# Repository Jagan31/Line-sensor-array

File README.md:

# PCB design of line sensor array in eagle software
1)LSA2.sch is the schematic file of the line sensor array.

2)LSA2.brd is the pcb layout file of the line sensor array.

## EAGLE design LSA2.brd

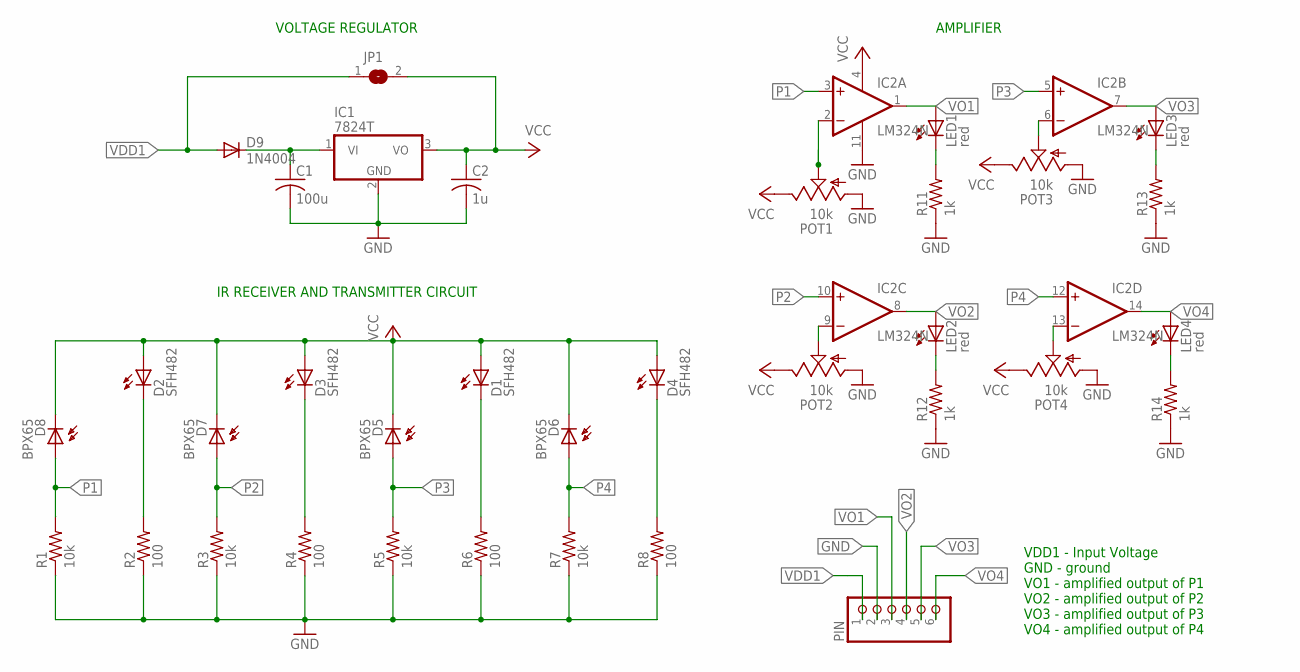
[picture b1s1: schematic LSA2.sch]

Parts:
C1: 100u; C0805
C2: 1u; C0805
D1, D2, D3, D4: SFH482
D5, D6, D7, D8: BPX65
D9: 1N4004; DO41-10
IC1: 7824T; TO220H
IC2: LM324N; DIL14
JP1: SJW
LED1, LED2, LED3, LED4: red; SMARTLED-TTW
PIN: PINHD-1X6/90; 1X06/90
POT1, POT2, POT3, POT4: 10k; 6MM
R1, R3, R5, R7: 10k; M0805
R2, R4, R6, R8: 100; M0805
R11, R12, R13, R14: 1k; M0805

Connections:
D5: D1.K (C), R6.2
GND: C1.2, C2.2, IC1.2 (GND), IC2.11 (V-), PIN.2, POT1.A, POT2.A, POT3.A, POT4.A, R11.1, R12.1, R13.1, R14.1
unnamed: C1.1, D9.C, IC1.1 (VI)
unnamed: D2.K (C), R2.2
unnamed: D3.K (C), R4.2
unnamed: D4.K (C), R8.2
unnamed: IC2.2 (-IN), POT1.S
unnamed: IC2.6 (-IN), POT3.S
unnamed: IC2.13 (-IN), POT4.S
unnamed: LED2.C@1 (C), R12.2
unnamed: LED4.C@1 (C), R14.2
unnamed: LED3.C@1 (C), R13.2
unnamed: LED1.C@1 (C), R11.2
P1: D8.A, IC2.3 (+IN), R1.2
P2: D7.A, IC2.10 (+IN), R3.2
P3: D5.A, IC2.5 (+IN), R5.2
P4: D6.A, IC2.12 (+IN), R7.2
POT2: IC2.9 (-IN), POT2.S
R6: R1.1, R2.1, R3.1, R4.1, R5.1, R6.1, R7.1, R8.1
VCC: C2.1, D1.A, D2.A, D3.A, D4.A, D5.K (C), D6.K (C), D7.K (C), D8.K (C), IC1.3 (VO), IC2.4 (V+), JP1.2, POT1.E, POT2.E, POT3.E, POT4.E
VDD1: D9.A, JP1.1, PIN.1
VO1: IC2.1 (OUT), LED1.A@1 (A), PIN.3
VO2: IC2.8 (OUT), LED2.A@1 (A), PIN.4
VO3: IC2.7 (OUT), LED3.A@1 (A), PIN.5
VO4: IC2.14 (OUT), LED4.A@1 (A), PIN.6

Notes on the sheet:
VOLTAGE REGULATOR
AMPLIFIER
VDD1 - Input Voltage GND - ground VO1 - amplified output of P1 VO2 - amplified output of P2 VO3 - amplified output of P3 VO4 - amplified output of P4
IR RECEIVER AND TRANSMITTER CIRCUIT

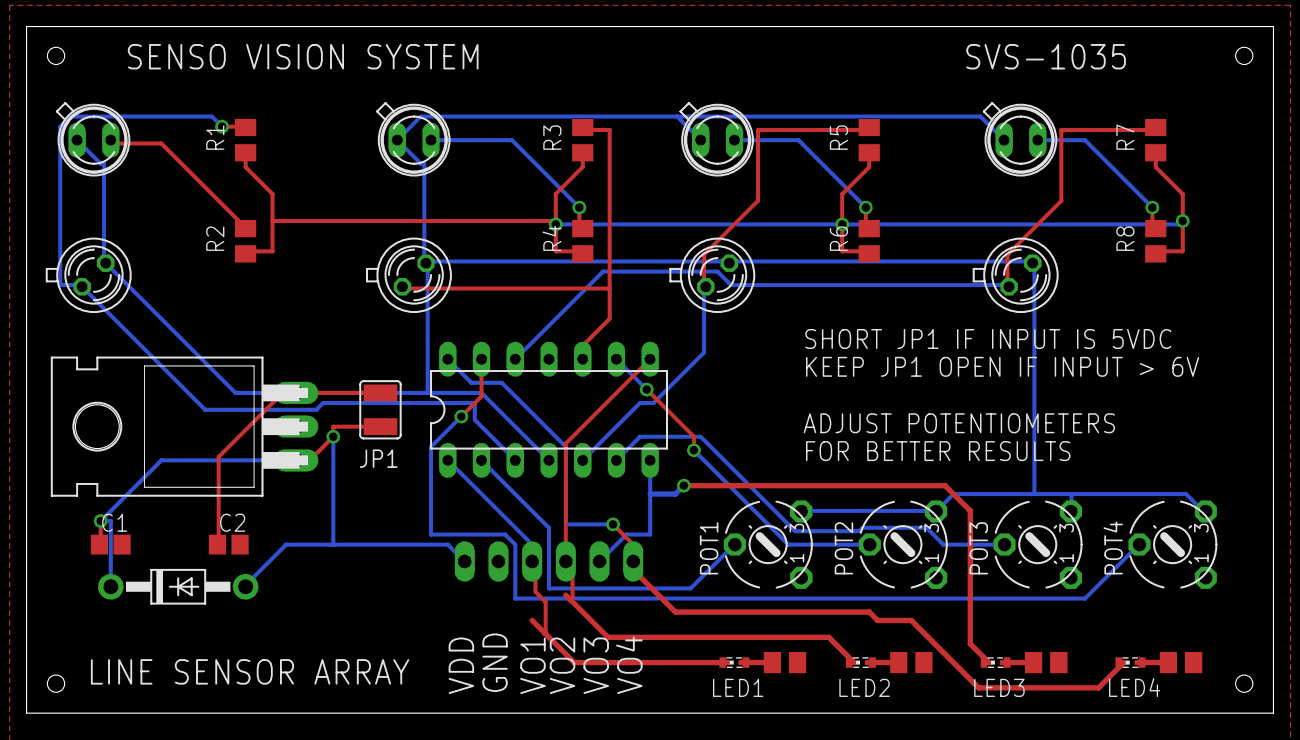
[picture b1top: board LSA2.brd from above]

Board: 2 copper layers, 94.0 x 51.7 mm, 35 parts (1 on the bottom side), 25 nets.

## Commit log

2016-04-08 Added files via upload
